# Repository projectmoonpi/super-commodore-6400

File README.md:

<p align="center"><b>Designed and Created by Project Moon Pi</b></p>

# Tidal Array 6400

Several **NTSC Commodore 64s** joined into one machine. Each C64 is a "core". One leader hands out work, and
every core, the leader included, computes its share. The goal is a pack of 8 or more C64s, sharing RAM through
a cartridge-port hub and running from one clock. Each machine added should make the whole thing about that much
faster, and the benchmark shows it on screen.

It is one of the [Project Moon Pi Commodore projects](https://github.com/projectmoonpi/commodore).

**Step 1 (this release): two C64s on a user-port cable.** It has the core kernel, the job protocol, and a
Mandelbrot benchmark with a live speed-up readout.

*Left: the leader's screen after the two-core run. The leader's own tiles are blue and cyan; core 1's are red,
orange and yellow. Right: core 1's own monitor, showing only the tiles it computed. Both are rendered from the
two-machine simulator's memory.*

## Results

| Cores | Simulator | VICE (real C64 timing) | Speed-up |
|---|---|---|---|
| 1 | 56.3 s | 60.2 s | 1.00× |
| 2 | 28.8 s | not tested: VICE can't link two C64s | **1.955×** |

That's 97.8% of a perfect doubling. The rest is the time spent passing tiles over the cable and the moment at
the end when one core finishes before the other.

The simulator doesn't count the cycles the VIC chip steals for the screen. That's the 7% gap on one core. Every
core loses the same share, so the speed-up is unchanged.

## What you need

- 2 NTSC C64s, each able to load the programs. Any of these works:
  - a disk drive with `ta6400.d64`, or an SD2IEC / Pi1541;
  - the `.prg` files on a Kung Fu Flash or other SD cartridge;
  - the cartridge images: `ta6400-leader.crt` and `ta6400-core.crt`. These are Magic Desk cartridges (32 KB
    and 16 KB) for a Kung Fu Flash, or burned to a Magic Desk-compatible EPROM cartridge. They start the
    program at power-on, and the reset button starts it again.
- A user-port-to-user-port cable (below).

## The cable

**Build it with the illustrated guide:
[Build Guide 1: the user-port link cable (PDF)](docs/guides/TA6400-Guide-1-Link-Cable.pdf).** It covers your
start and end goals, drawings of the finished cable and of the two C64s hooked up, a schematic, the parts
with DigiKey part numbers, how to find pin 1 on your C64, colour-coded wiring
and solder maps, numbered steps, a digital-multimeter test checklist, the first run, and troubleshooting. The table below
is the short version.

Two 24-pin (2×12, 0.156") user-port edge connectors, wired:

| Signal | C64 A pin | C64 B pin |
|---|---|---|
| PB0–PB7 (data) | C, D, E, F, H, J, K, L | C, D, E, F, H, J, K, L (straight through) |
| PC2 → FLAG | 8 | B |
| FLAG ← PC2 | B | 8 |
| GND | 1, 12, A, N | 1, 12, A, N |

Leave everything else unconnected. Never connect +5 V (pin 2), RESET (3) or 9 V AC (10, 11).

For safety, put a 330 Ω resistor in series with each data line (PB0–PB7). If a program ever drove the lines
from both ends at once, the resistors limit the current. The protocol never does this (the simulator counts
it, and it stayed at 0), but other software could. The resistors don't slow the link.

## Running it

1. Switch on the worker C64 and load the core: `LOAD"PACK CORE",8` then `RUN`, or plug in the core cartridge. It shows **CORE: WAITING FOR THE
   LEADER**.
2. On the leader C64: `LOAD"PACK LEADER",8` then `RUN`, or use the leader cartridge. It scans the cable, uploads the job to the core, and
   shows **CORES 2**. The core's screen changes to **CORE 1: LINKED TO THE LEADER**.
3. Press **1** to run on the leader alone, then **2** to run on both. Each result shows its time and its
   speed-up over the 1-core run. Press **S** to scan the cable again, for example after switching a core on.

## How it works

**The link.** Port B of CIA 2 carries 8 data bits. Every read or write of port B pulses PC2, which the other
machine sees on its FLAG input:
- writing a byte says "here is a byte";
- reading it says "got it".

That gives a fully handshaked byte transfer of about 30 cycles, around 30 KB/s. The leader drives the data
lines. When a core answers, the two sides hand the lines over with a "line free" pulse, so they never drive
at the same time.

**The core kernel** (`src/common.asm`) is a few hundred bytes. It obeys three commands:

| Command | Bytes | What the core does |
|---|---|---|
| WRITE | `$01` addr len data… | stores the data in its memory |
| READ | `$02` addr len | sends that memory back |
| CALL | `$03` addr A | runs `JSR addr` with A, then pulses "done" |

The cores are generic: the leader uploads the job (5 KB) when it finds a core. The same program could hand
out any other work.

**The benchmark** (`src/job.asm`) draws the whole Mandelbrot set at 160×160 multicolour pixels, in 200 tiles
of 16×8.
- Tiles are handed out one at a time, to whichever core is free, so fast and slow tiles balance out.
- The leader computes tiles too. After every 4 pixels it checks the cable. When the core says "done", the
  leader collects the tile's 32 bytes and gives the core the next one.
- Maths: 8.8 fixed point, at about 200 cycles an iteration. While a point is in play |z| < 2, so each value's
  high byte is 0 or 1. A square is then a table look-up, and a product is one 8×8 quarter-square multiply.

**Timing.** CIA 1's timer A counts cycles and timer B counts timer A's underflows, giving an exact 32-bit
cycle count.

## Building and testing

`./build.sh` assembles everything with ACME, writes `build/ta6400.d64` and the two cartridge images
(`src/cart.asm`, `tools/make_crt.py`), and runs the test.

VICE 3.8 can't connect two C64s through their user ports. So `tools/packsim.c` simulates two C64s joined by
the cable:
- a 6510 with all documented opcodes and cycle counts;
- the memory map, CIA timers and raster interrupts;
- port B, PC2 and FLAG, wired as above.

`tools/simcheck.py` then checks the result:
- runs the auto-test leader (`-DAUTO=1`: 1 core, then all cores);
- compares every tile with a Python copy of the job's maths;
- counts which core did which tile;
- reports any contention on the cable;
- writes `build/sim-0.png` and `build/sim-1.png`.

The leader's picture from VICE matches the simulator's byte for byte.

## Roadmap

1. **Two C64s, user-port cable.** Software, protocol and benchmark. *This release: tested in simulation and in
   VICE; real hardware next.*
2. **Clock-injection bench test.** One 14.31818 MHz master clock fed to two C64s, with the crystal left in
   place but bypassed. The mod board must suit every motherboard revision (250407, 250425, 250466 and 250469),
   set with a switch or jumpers. The test also checks that the hub can line the machines up by dropping clock
   pulses.
3. **Pack Link pod and a 2-port hub.** A cartridge-port pod in each C64, ribbon cables, and an FPGA hub with
   fast shared SRAM, mailboxes and IRQs. That gives full-speed shared memory instead of a cable.
4. **The 8-port hub.** An 8-core benchmark and the video wall.

## Credits

- **Design, code and the Project Moon Pi logo.** Project Moon Pi.
- **Character set.** Copied at run time from the C64's own character ROM (© Commodore). It is not included
  here. The simulator reads VICE's copy for its renders.
- **ACME** cross-assembler. Marco Baye and contributors (GPL).
- **VICE** emulator and `c1541`. The VICE team (GPL).
- **Python and Pillow.** Their authors (PSF / HPND licences).
- **Palette values.** The "colodore" C64 palette by Philip "Pepto" Timmermann.
- **B612 typeface** (the build guide's cover). Airbus and Intactile Design (SIL Open Font License 1.1, see
  `tools/guide/fonts/OFL.txt`).
- **ReportLab** (the build guide). ReportLab Inc. (BSD).
- **Quarter-square multiplication.** A classic 6502 technique, as documented on codebase64.org.
- **User port pinout and CIA behaviour.** The *Commodore 64 Programmer's Reference Guide* and the MOS 6526
  datasheet.
- Built with Claude Code (Anthropic).

Commodore 64 is a trademark of its owners. Project Moon Pi is not affiliated with them.

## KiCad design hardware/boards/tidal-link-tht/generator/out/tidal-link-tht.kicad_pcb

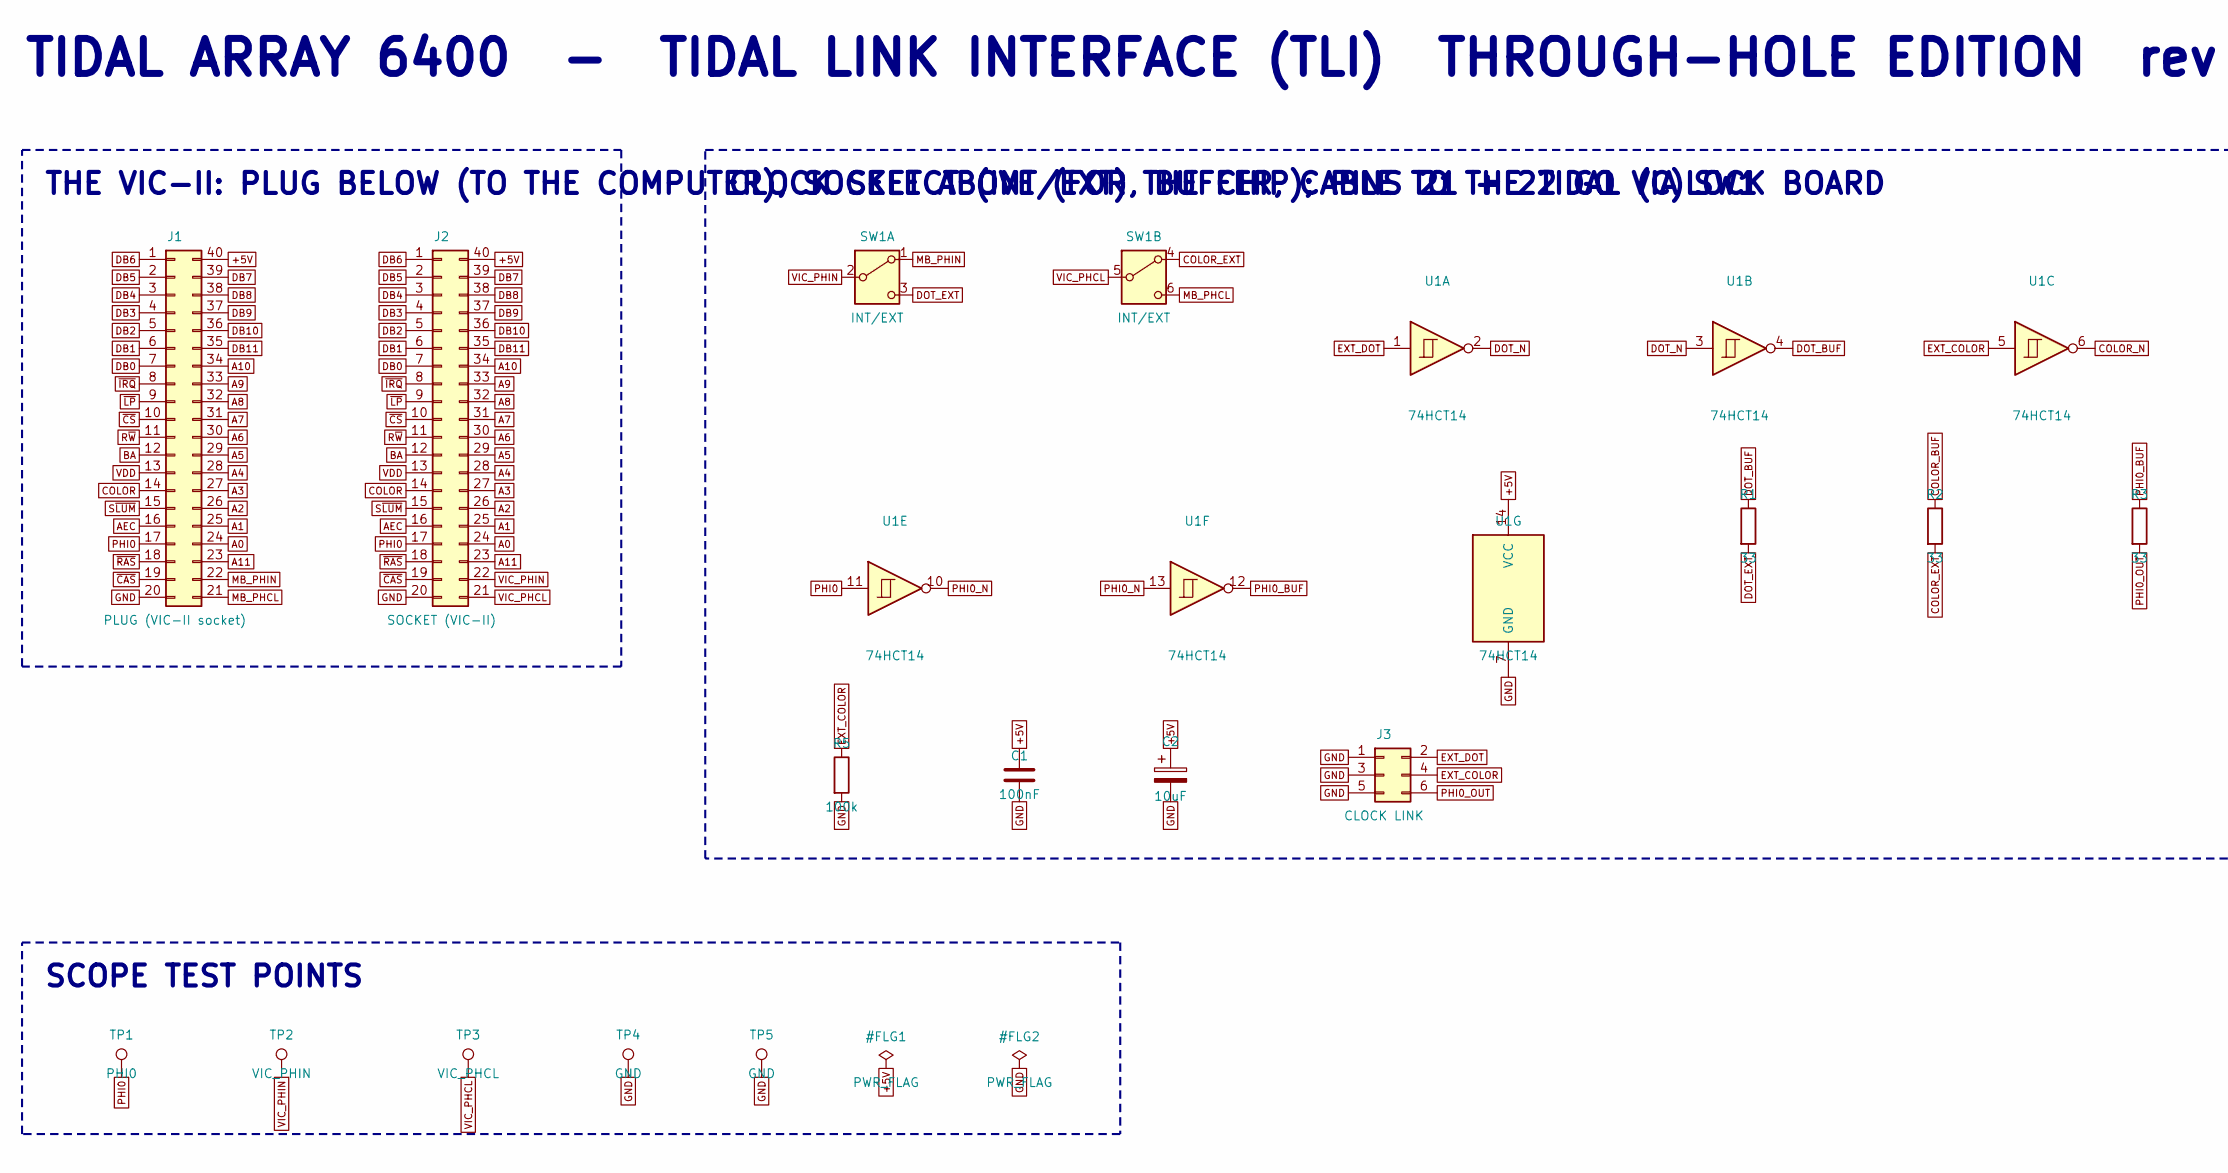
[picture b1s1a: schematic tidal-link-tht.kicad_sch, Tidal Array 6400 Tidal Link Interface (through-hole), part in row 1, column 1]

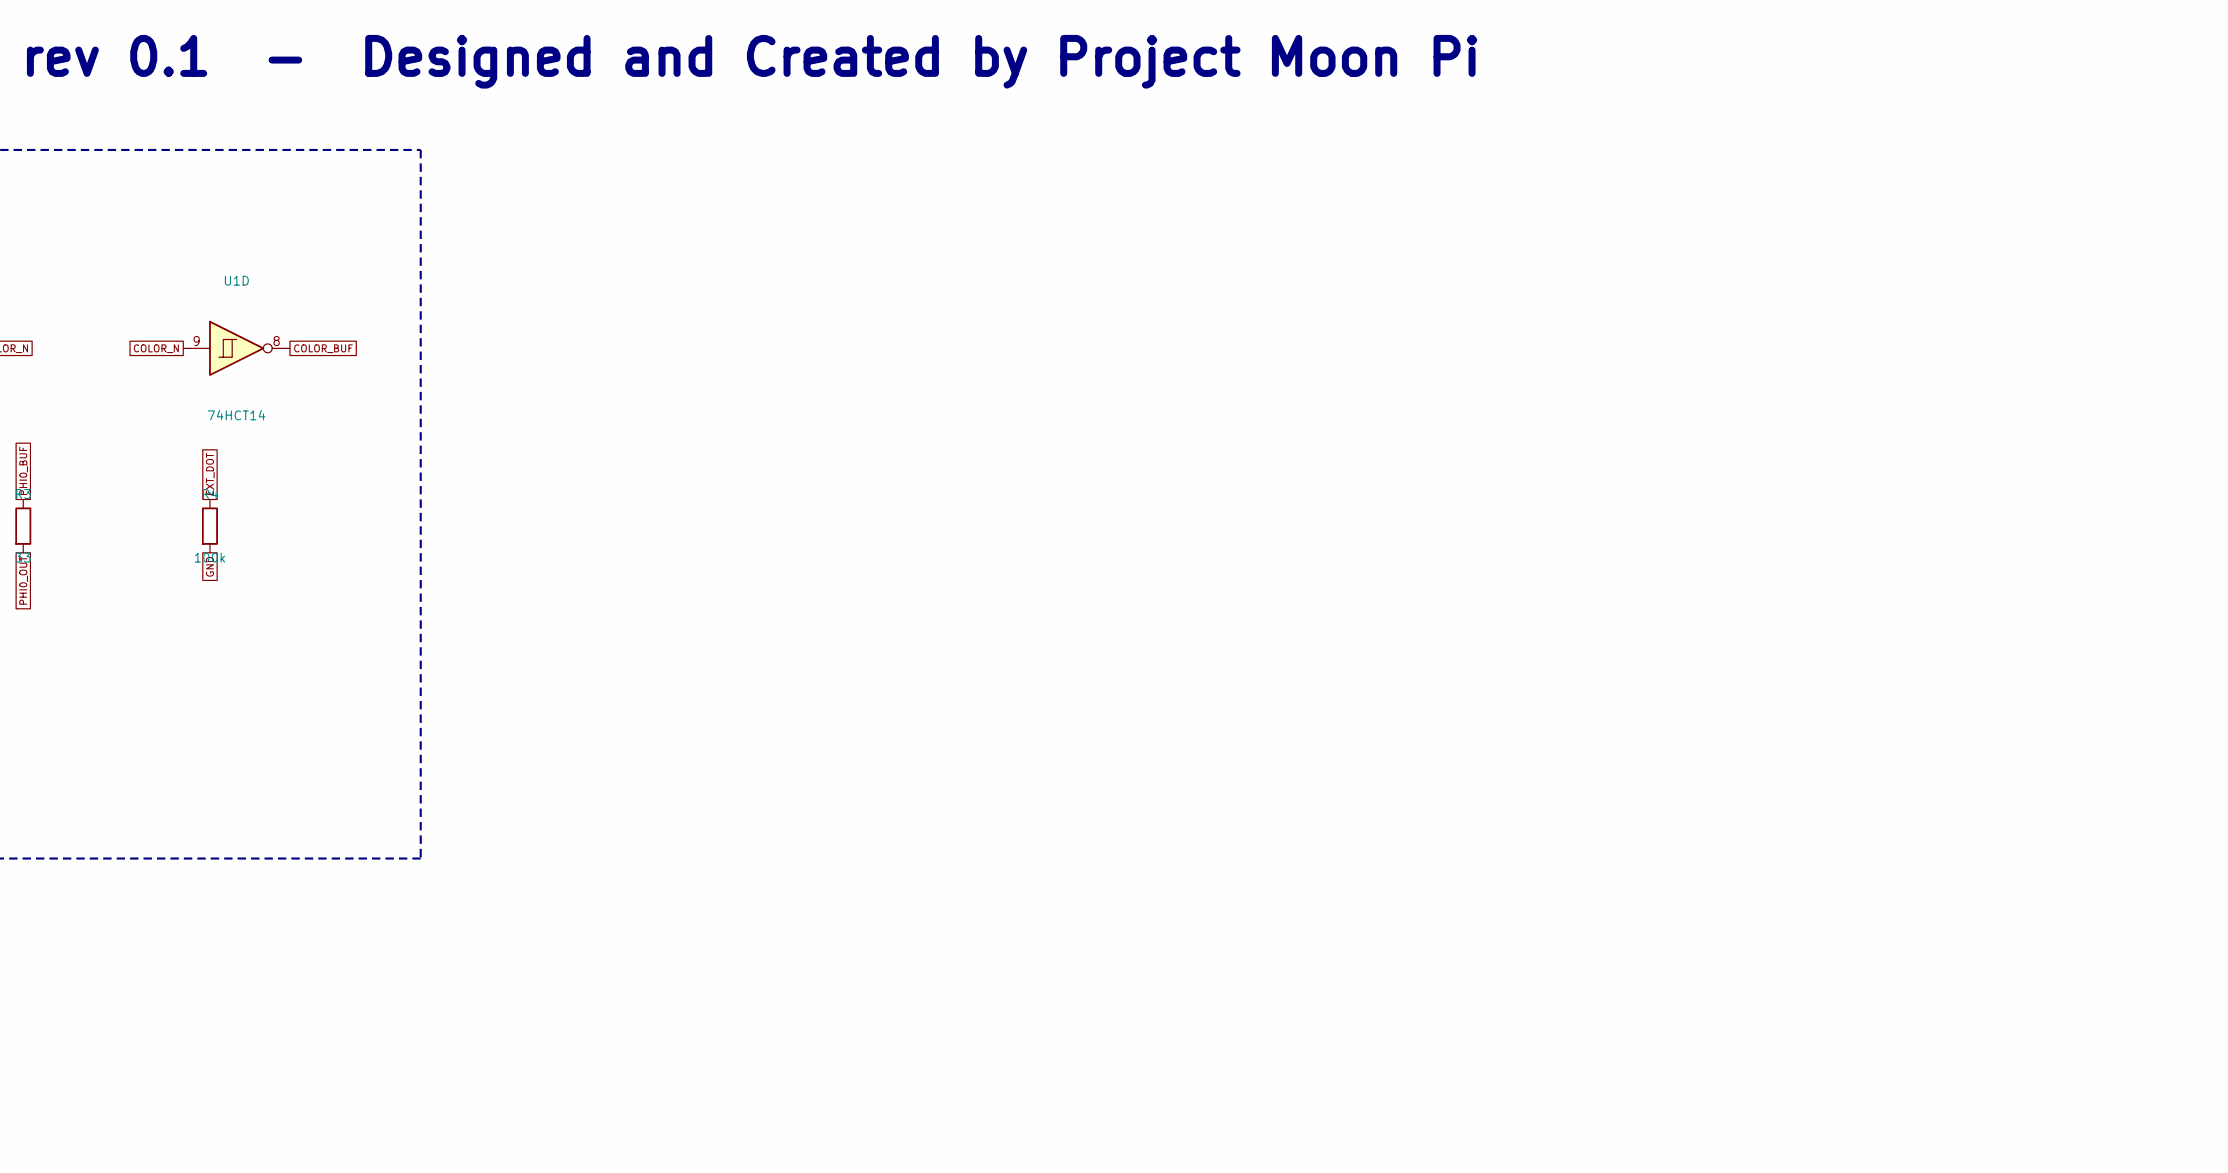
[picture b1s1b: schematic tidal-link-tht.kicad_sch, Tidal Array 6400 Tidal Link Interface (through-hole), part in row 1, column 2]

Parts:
C1: 100nF; C_Rect_L4.0mm_W2.5mm_P2.50mm; MPN FG18X7R1H104KNT06
C2: 10uF; CP_Radial_D5.0mm_P2.00mm; MPN ESK106M025AC3AA
J1: PLUG (VIC-II socket); DIP-40_W15.24mm; MPN 350-10-164-00-006000 (one 64-pin strip,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
J2: SOCKET (VIC-II); DIP-40_W15.24mm; MPN 310-87-120-41-001101 (x2)
J3: CLOCK LINK; IDC-Header_2x03_P2.54mm_Vertical; MPN 61200621621
R1, R2, R3: 33; R_Axial_DIN0207_L6.3mm_D2.5mm_P7.62mm_Horizontal; MPN MFR-25FBF52-33R
R4, R5: 100k; R_Axial_DIN0207_L6.3mm_D2.5mm_P7.62mm_Horizontal; MPN MFR-25FRF52-100K
SW1: INT/EXT; SW_CK_JS202011CQN_DPDT_Straight; MPN JS202011CQN
TP1: PHI0; TestPoint_Keystone_5000-5004_Miniature; MPN 5002
TP2: VIC_PHIN; TestPoint_Keystone_5000-5004_Miniature; MPN 5004
TP3: VIC_PHCL; TestPoint_Keystone_5000-5004_Miniature; MPN 5003
TP4, TP5: GND; TestPoint_Keystone_5000-5004_Miniature; MPN 5001
U1: 74HCT14; DIP-14_W7.62mm_Socket; MPN SN74HCT14N

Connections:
+5V: C1.1, C2.1, J1.40, J2.40, U1.14 (VCC)
A0: J1.24, J2.24
A1: J1.25, J2.25
A2: J1.26, J2.26
A3: J1.27, J2.27
A4: J1.28, J2.28
A5: J1.29, J2.29
A6: J1.30, J2.30
A7: J1.31, J2.31
A8: J1.32, J2.32
A9: J1.33, J2.33
A10: J1.34, J2.34
A11: J1.23, J2.23
AEC: J1.16, J2.16
BA: J1.12, J2.12
COLOR: J1.14, J2.14
COLOR_BUF: R2.1, U1.8
COLOR_EXT: R2.2, SW1.4 (A)
COLOR_N: U1.6, U1.9
DB0: J1.7, J2.7
DB1: J1.6, J2.6
DB2: J1.5, J2.5
DB3: J1.4, J2.4
DB4: J1.3, J2.3
DB5: J1.2, J2.2
DB6: J1.1, J2.1
DB7: J1.39, J2.39
DB8: J1.38, J2.38
DB9: J1.37, J2.37
DB10: J1.36, J2.36
DB11: J1.35, J2.35
DOT_BUF: R1.1, U1.4
DOT_EXT: R1.2, SW1.3 (C)
DOT_N: U1.2, U1.3
EXT_COLOR: J3.4, R5.1, U1.5
EXT_DOT: J3.2, R4.1, U1.1
GND: C1.2, C2.2, J1.20, J2.20, J3.1, J3.3, J3.5, R4.2, R5.2, TP4.1, TP5.1, U1.7 (GND)
MB_PHCL: J1.21, SW1.6 (C)
MB_PHIN: J1.22, SW1.1 (A)
PHI0: J1.17, J2.17, TP1.1, U1.11
PHI0_BUF: R3.1, U1.12
PHI0_N: U1.10, U1.13
PHI0_OUT: J3.6, R3.2
R~W: J1.11, J2.11
S~LUM: J1.15, J2.15
VDD: J1.13, J2.13
VIC_PHCL: J2.21, SW1.5 (B), TP3.1
VIC_PHIN: J2.22, SW1.2 (B), TP2.1
~CAS: J1.19, J2.19
~CS: J1.10, J2.10
~IRQ: J1.8, J2.8
~LP: J1.9, J2.9
~RAS: J1.18, J2.18

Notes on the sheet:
THE VIC-II: PLUG BELOW (TO THE COMPUTER), SOCKET ABOVE (FOR THE CHIP); PINS 21 + 22 GO VIA SW1
CLOCK SELECT (INT/EXT), BUFFER, CABLE TO THE TIDAL (C)LOCK BOARD
SCOPE TEST POINTS
TIDAL ARRAY 6400 - TIDAL LINK INTERFACE (TLI) THROUGH-HOLE EDITION rev 0.1 - Designed and Created by Project Moon Pi

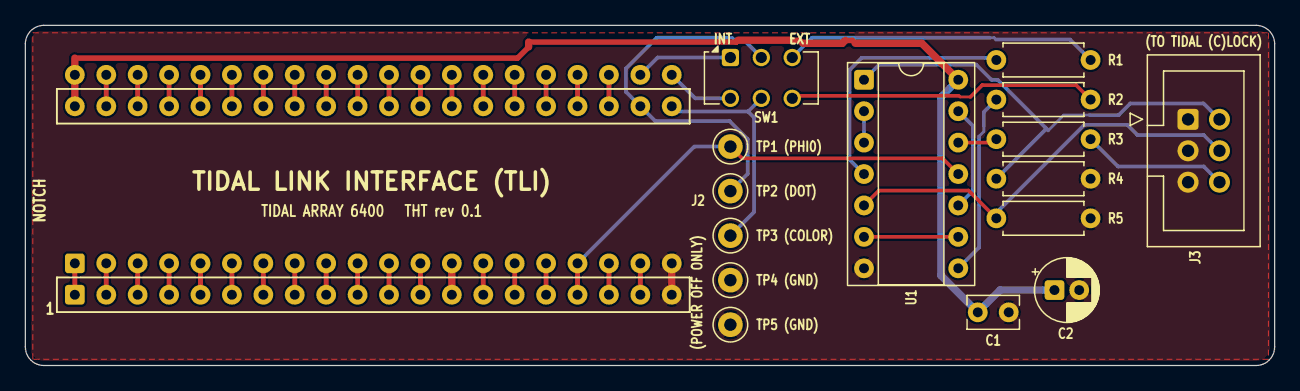
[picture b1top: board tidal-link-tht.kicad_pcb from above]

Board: 2 copper layers, 101.0 x 27.5 mm, 17 parts (0 on the bottom side), 53 nets.

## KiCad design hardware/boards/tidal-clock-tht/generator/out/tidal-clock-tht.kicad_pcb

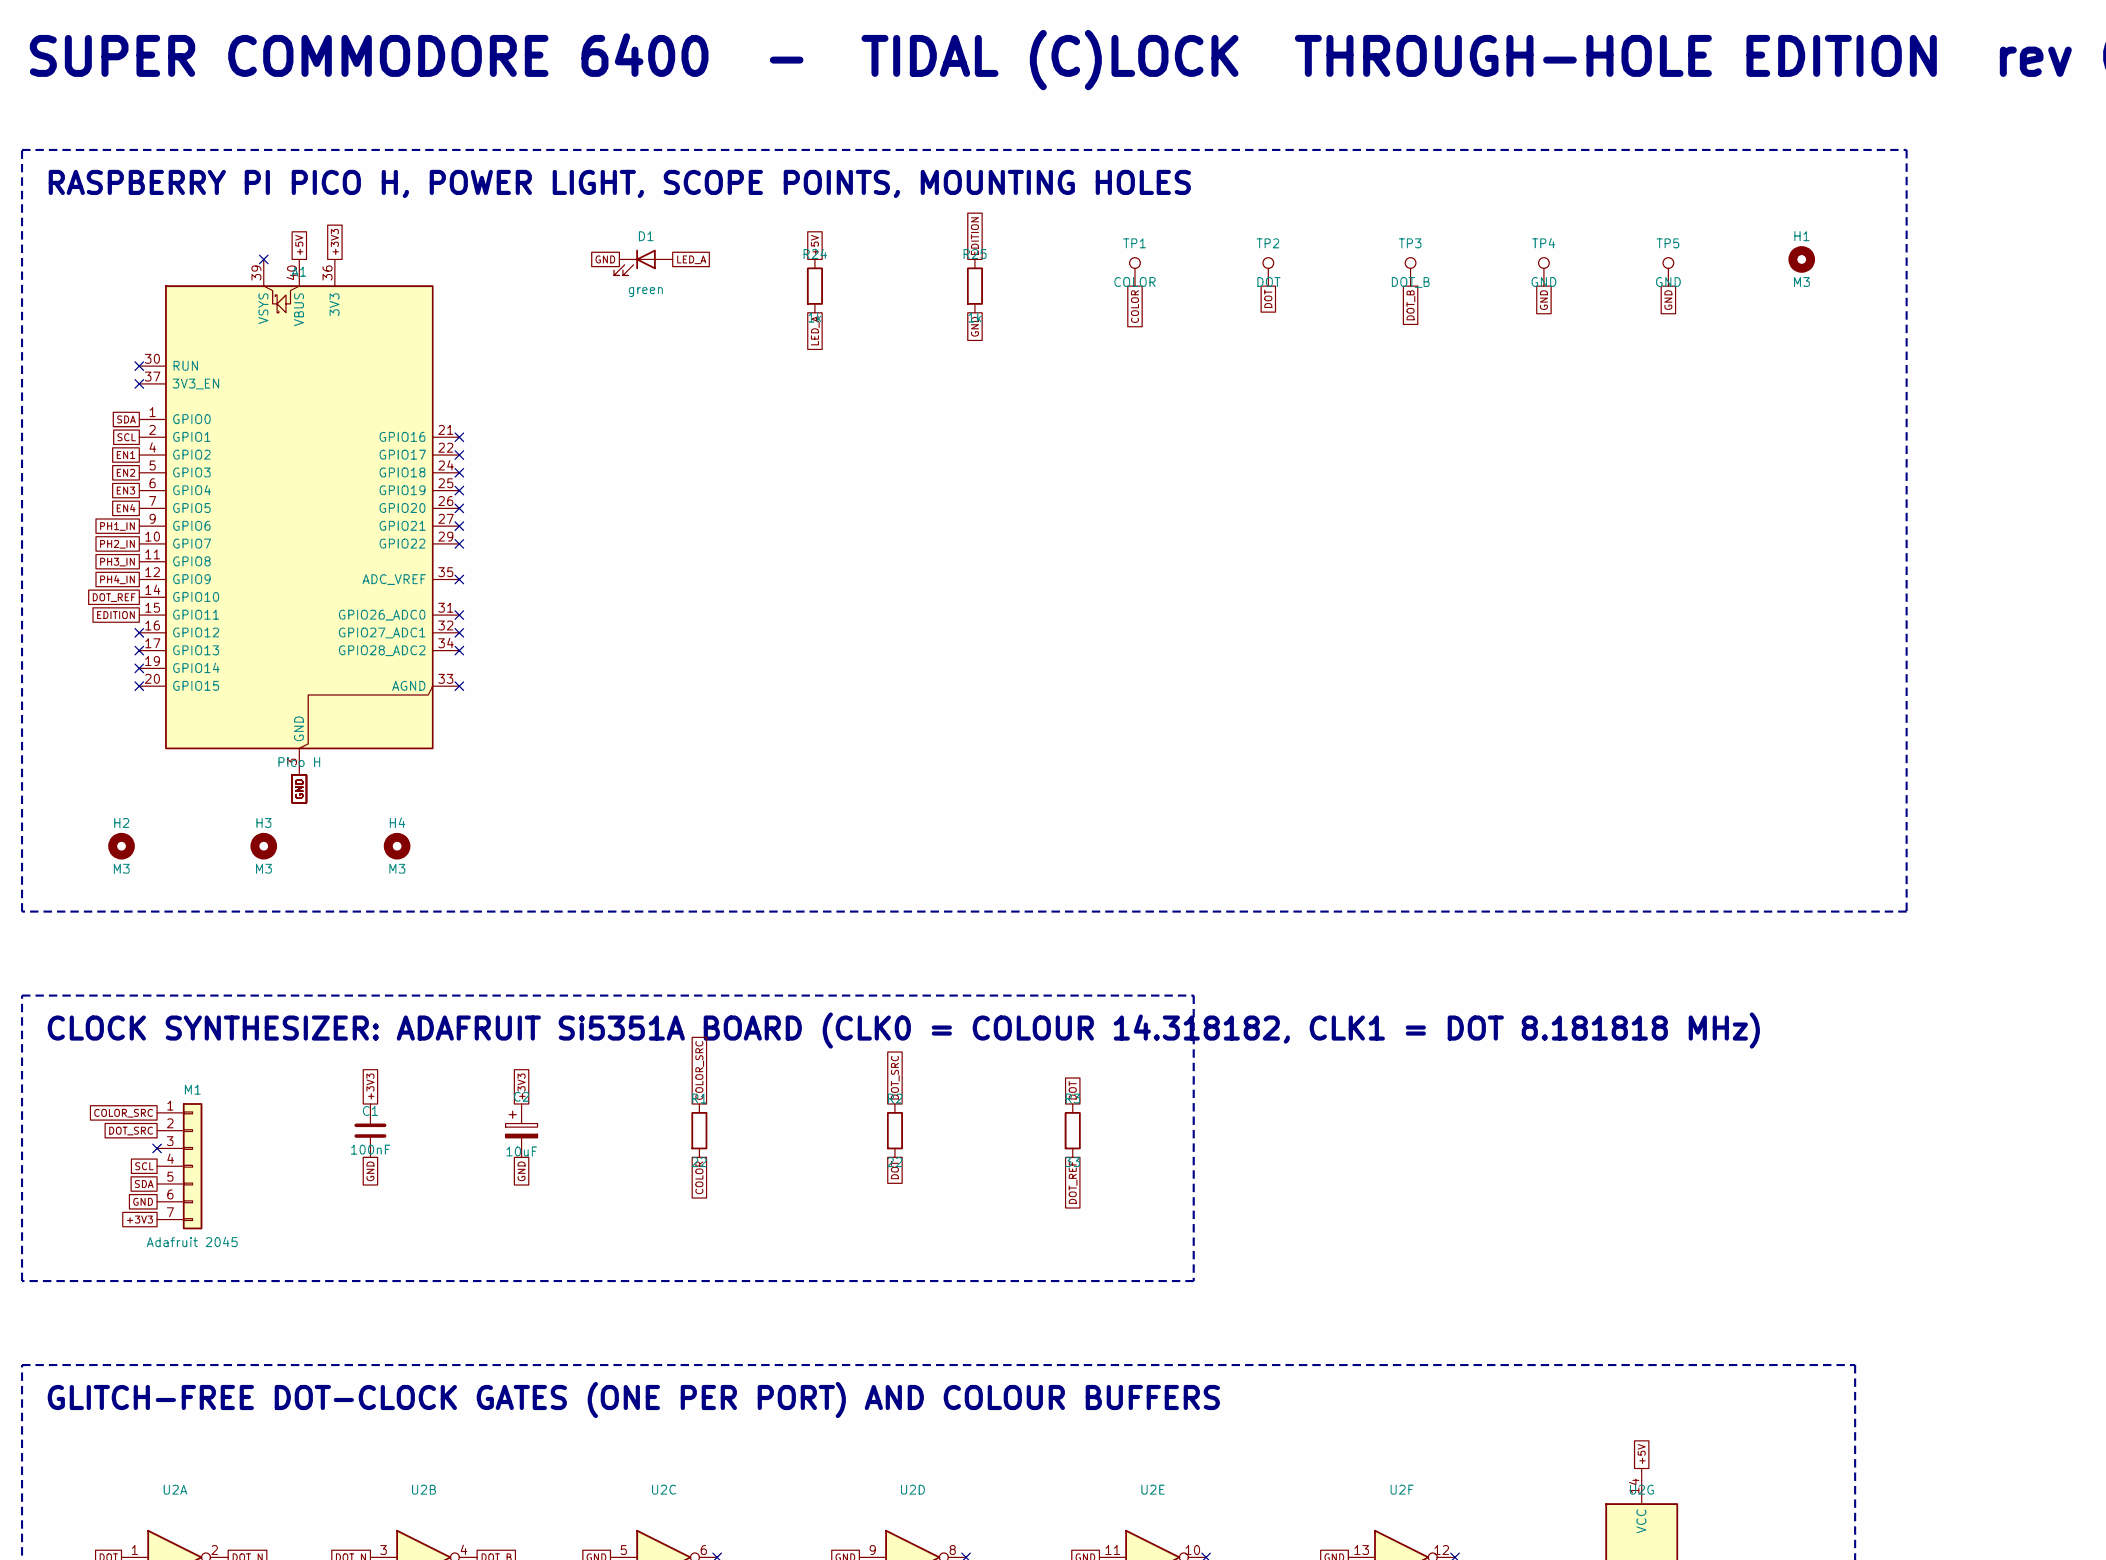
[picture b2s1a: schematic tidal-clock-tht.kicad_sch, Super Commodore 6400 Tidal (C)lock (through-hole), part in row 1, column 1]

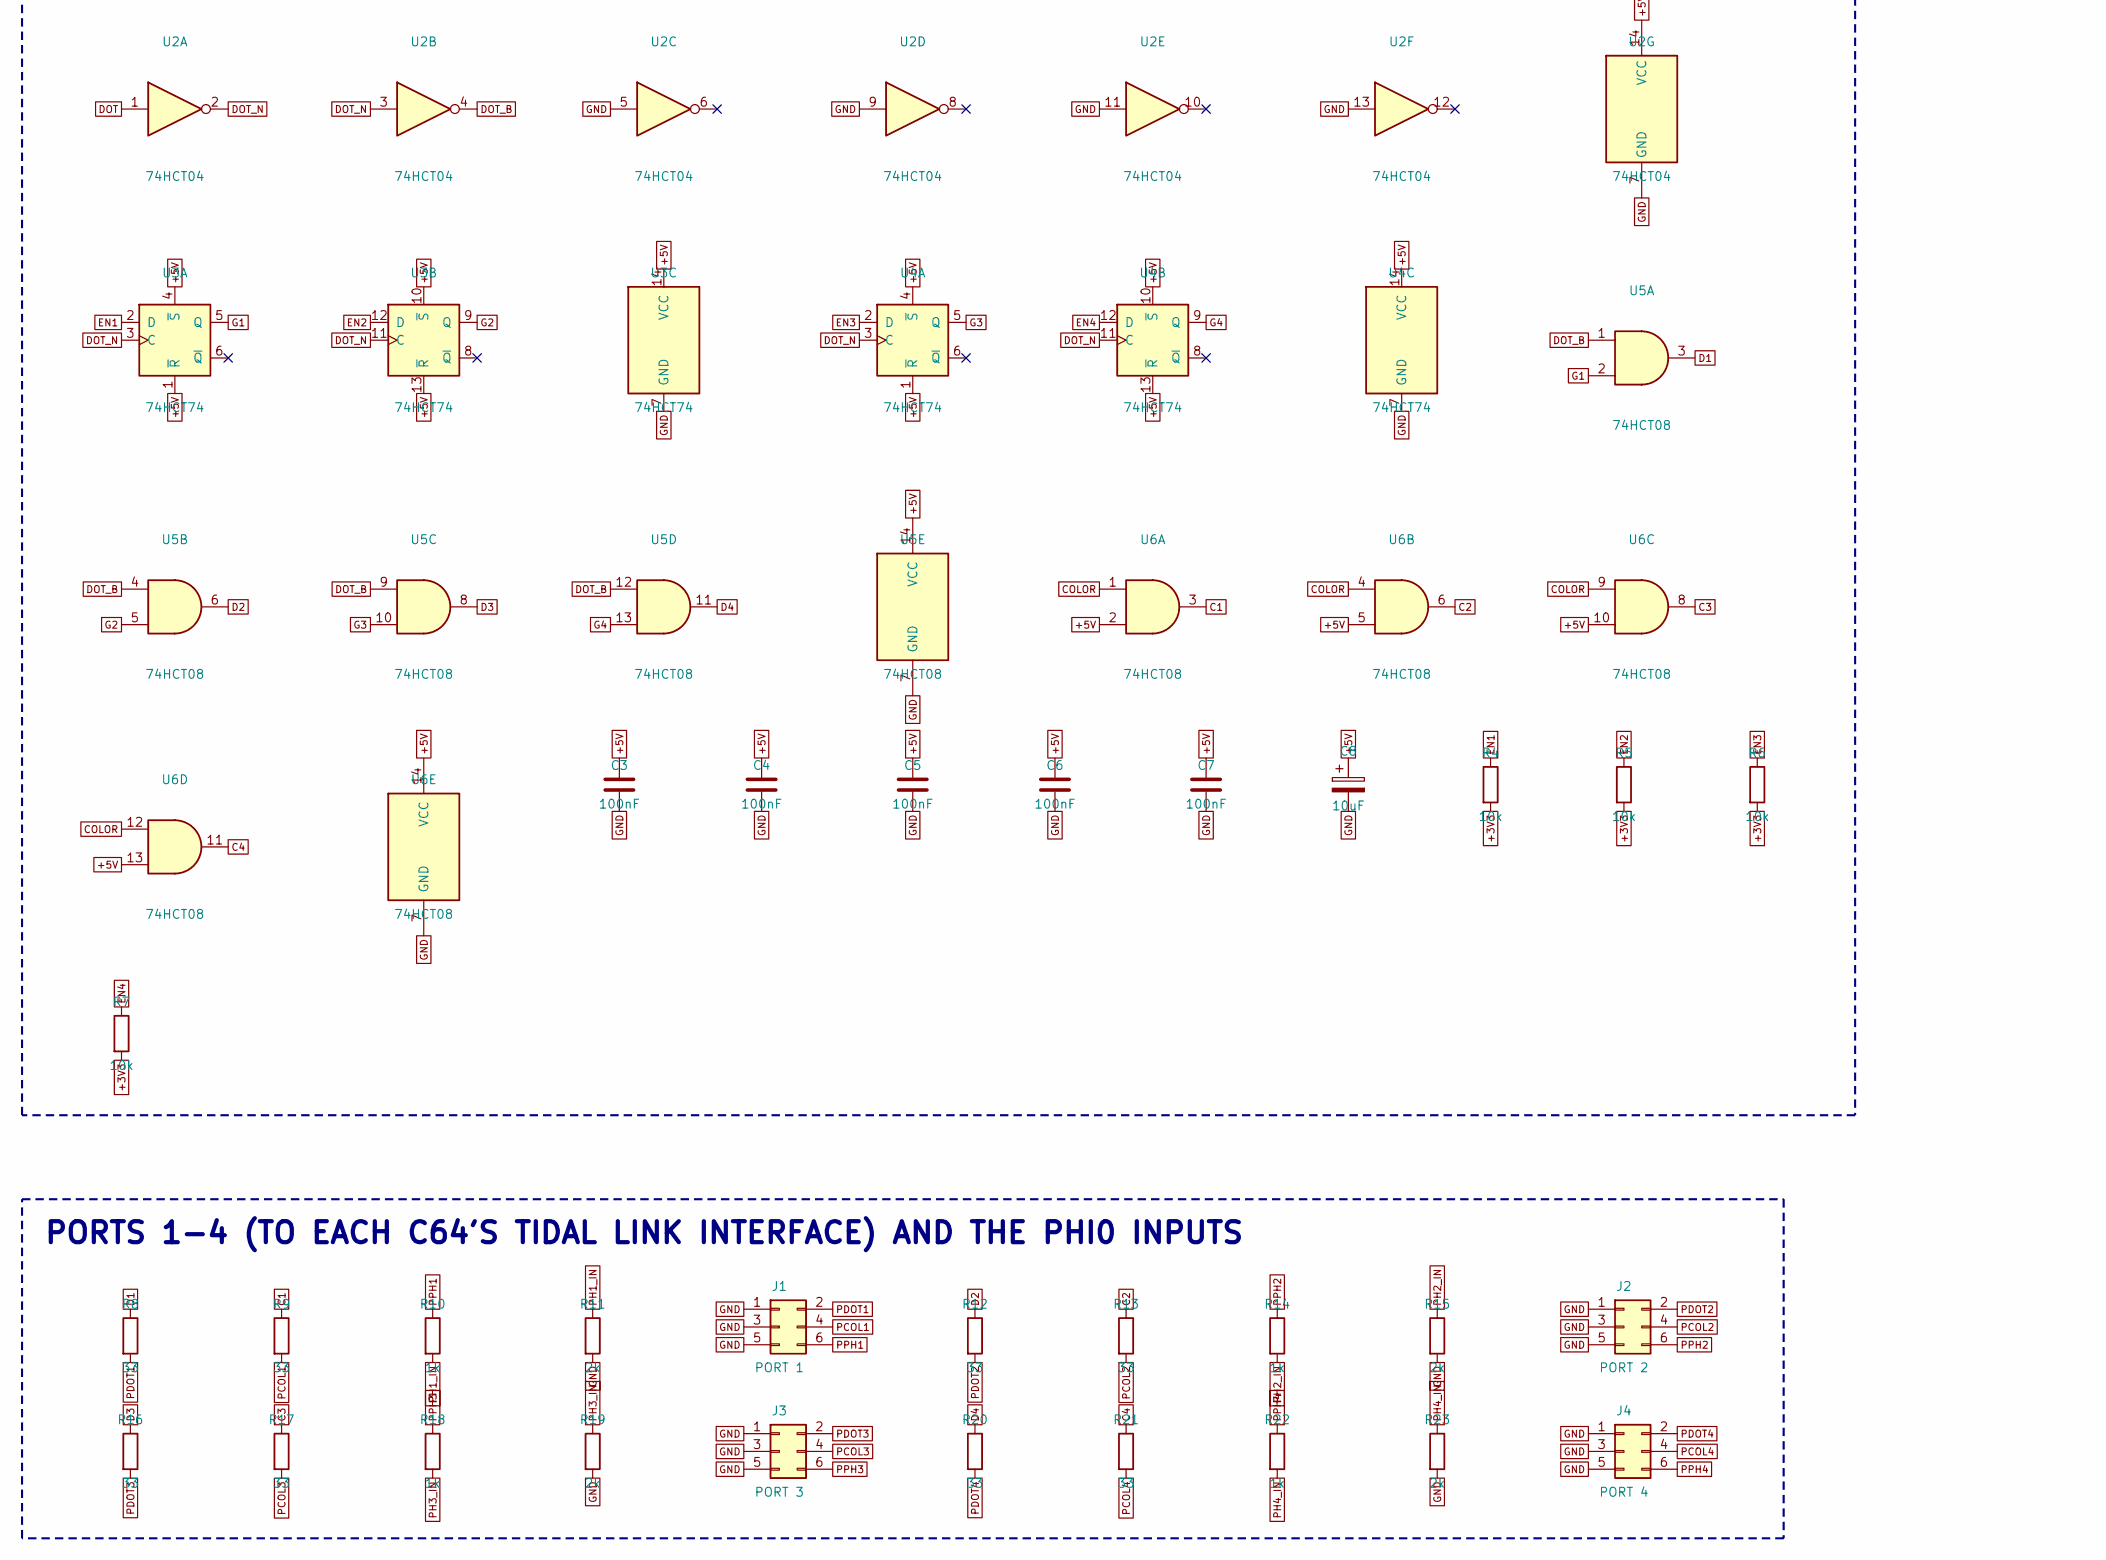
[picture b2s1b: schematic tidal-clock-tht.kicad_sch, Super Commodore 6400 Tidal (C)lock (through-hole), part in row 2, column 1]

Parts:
A1: Pico H; RaspberryPi_Pico_Common_THT; MPN SC0917
C1, C3, C4, C5, C6, C7: 100nF; C_Rect_L4.0mm_W2.5mm_P2.50mm; MPN FG18X7R1H104KNT06
C2, C8: 10uF; CP_Radial_D5.0mm_P2.00mm; MPN ESK106M025AC3AA
D1: green; LED_D3.0mm; MPN LTL-4231N
H1, H2, H3, H4: M3; MountingHole_3.2mm_M3
J1: PORT 1; IDC-Header_2x03_P2.54mm_Vertical; MPN 61200621621
J2: PORT 2; IDC-Header_2x03_P2.54mm_Vertical; MPN 61200621621
J3: PORT 3; IDC-Header_2x03_P2.54mm_Vertical; MPN 61200621621
J4: PORT 4; IDC-Header_2x03_P2.54mm_Vertical; MPN 61200621621
M1: Adafruit 2045; PinSocket_1x07_P2.54mm_Vertical; MPN 2045
R1, R2: 22; R_Axial_DIN0207_L6.3mm_D2.5mm_P10.16mm_Horizontal; MPN MFR-25FBF52-22R
R3, R8, R9, R12, R13, R16, R17, R20, R21: 33; R_Axial_DIN0207_L6.3mm_D2.5mm_P10.16mm_Horizontal; MPN MFR-25FBF52-33R
R4, R5, R6, R7: 10k; R_Axial_DIN0207_L6.3mm_D2.5mm_P10.16mm_Horizontal; MPN MFR-25FBF52-10K
R10, R14, R18, R22, R24, R25: 1k; R_Axial_DIN0207_L6.3mm_D2.5mm_P10.16mm_Horizontal; MPN MFR-25FBF52-1K
R11, R15, R19, R23: 2k; R_Axial_DIN0207_L6.3mm_D2.5mm_P10.16mm_Horizontal; MPN MFR-25FBF52-2K
TP1: COLOR; TestPoint_Keystone_5000-5004_Miniature; MPN 5003
TP2: DOT; TestPoint_Keystone_5000-5004_Miniature; MPN 5004
TP3: DOT_B; TestPoint_Keystone_5000-5004_Miniature; MPN 5002
TP4, TP5: GND; TestPoint_Keystone_5000-5004_Miniature; MPN 5001
U2: 74HCT04; DIP-14_W7.62mm_Socket; MPN SN74HCT04N
U3, U4: 74HCT74; DIP-14_W7.62mm_Socket; MPN SN74HCT74N
U5, U6: 74HCT08; DIP-14_W7.62mm_Socket; MPN SN74HCT08N

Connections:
+3V3: A1.36 (3V3), C1.1, C2.1, M1.7, R4.2, R5.2, R6.2, R7.2
+5V: A1.40 (VBUS), C3.1, C4.1, C5.1, C6.1, C7.1, C8.1, R24.1, U2.14 (VCC), U3.1 (~R), U3.4 (~S), U3.10 (~S), U3.13 (~R), U3.14 (VCC), U4.1 (~R), U4.4 (~S), U4.10 (~S), U4.13 (~R), U4.14 (VCC), U5.14 (VCC), U6.2, U6.5, U6.10, U6.13, U6.14 (VCC)
C1: R9.1, U6.3
C2: R13.1, U6.6
C3: R17.1, U6.8
C4: R21.1, U6.11
COLOR: R1.2, TP1.1, U6.1, U6.4, U6.9, U6.12
COLOR_SRC: M1.1, R1.1
D1: R8.1, U5.3
D2: R12.1, U5.6
D3: R16.1, U5.8
D4: R20.1, U5.11
DOT: R2.2, R3.1, TP2.1, U2.1
DOT_B: TP3.1, U2.4, U5.1, U5.4, U5.9, U5.12
DOT_N: U2.2, U2.3, U3.3 (C), U3.11 (C), U4.3 (C), U4.11 (C)
DOT_REF: A1.14 (GPIO10), R3.2
DOT_SRC: M1.2, R2.1
EDITION: A1.15 (GPIO11), R25.1
EN1: A1.4 (GPIO2), R4.1, U3.2 (D)
EN2: A1.5 (GPIO3), R5.1, U3.12 (D)
EN3: A1.6 (GPIO4), R6.1, U4.2 (D)
EN4: A1.7 (GPIO5), R7.1, U4.12 (D)
G1: U3.5 (Q), U5.2
G2: U3.9 (Q), U5.5
G3: U4.5 (Q), U5.10
G4: U4.9 (Q), U5.13
GND: A1.3 (GND), A1.8 (GND), A1.13 (GND), A1.18 (GND), A1.23 (GND), A1.28 (GND), A1.38 (GND), C1.2, C2.2, C3.2, C4.2, C5.2, C6.2, C7.2, C8.2, D1.1 (K), J1.1, J1.3, J1.5, J2.1, J2.3, J2.5, J3.1, J3.3, J3.5, J4.1, J4.3, J4.5, M1.6, R11.2, R15.2, R19.2, R23.2, R25.2, TP4.1, TP5.1, U2.5, U2.7 (GND), U2.9, U2.11, U2.13, U3.7 (GND), U4.7 (GND), U5.7 (GND), U6.7 (GND)
LED_A: D1.2 (A), R24.2
PCOL1: J1.4, R9.2
PCOL2: J2.4, R13.2
PCOL3: J3.4, R17.2
PCOL4: J4.4, R21.2
PDOT1: J1.2, R8.2
PDOT2: J2.2, R12.2
PDOT3: J3.2, R16.2
PDOT4: J4.2, R20.2
PH1_IN: A1.9 (GPIO6), R10.2, R11.1
PH2_IN: A1.10 (GPIO7), R14.2, R15.1
PH3_IN: A1.11 (GPIO8), R18.2, R19.1
PH4_IN: A1.12 (GPIO9), R22.2, R23.1
PPH1: J1.6, R10.1
PPH2: J2.6, R14.1
PPH3: J3.6, R18.1
PPH4: J4.6, R22.1
SCL: A1.2 (GPIO1), M1.4
SDA: A1.1 (GPIO0), M1.5

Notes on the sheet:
RASPBERRY PI PICO H, POWER LIGHT, SCOPE POINTS, MOUNTING HOLES
CLOCK SYNTHESIZER: ADAFRUIT Si5351A BOARD (CLK0 = COLOUR 14.318182, CLK1 = DOT 8.181818 MHz)
GLITCH-FREE DOT-CLOCK GATES (ONE PER PORT) AND COLOUR BUFFERS
PORTS 1-4 (TO EACH C64'S TIDAL LINK INTERFACE) AND THE PHI0 INPUTS
SUPER COMMODORE 6400 - TIDAL (C)LOCK THROUGH-HOLE EDITION rev 0.1 - Designed and Created by Project Moon Pi

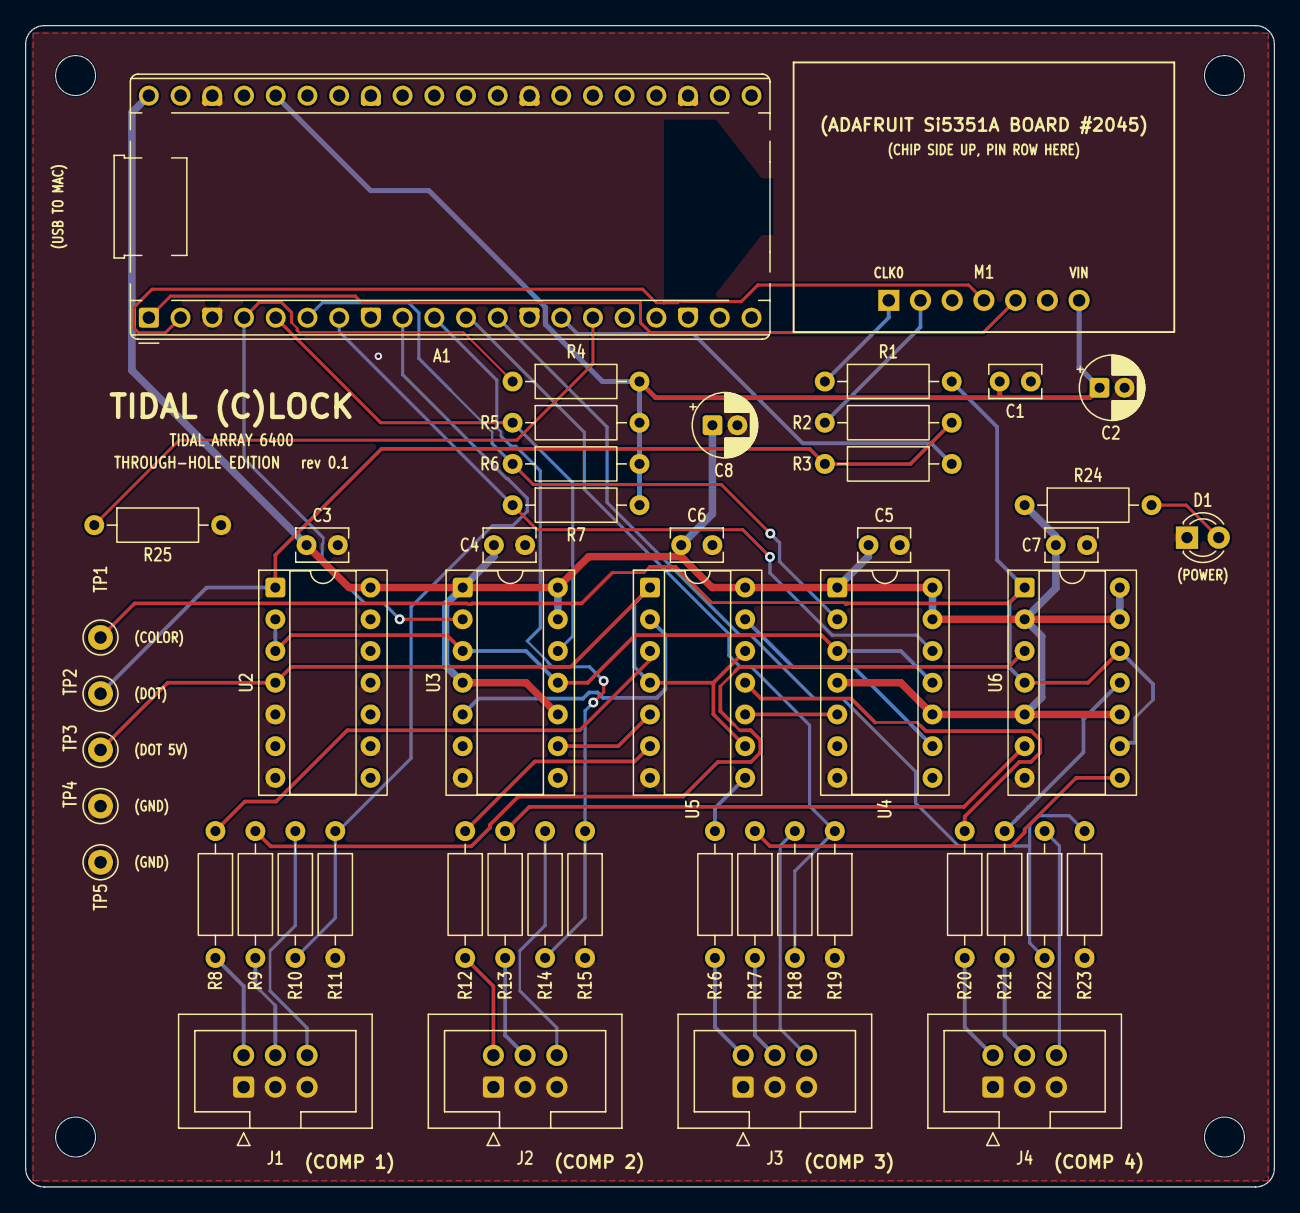
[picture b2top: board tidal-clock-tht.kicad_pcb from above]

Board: 2 copper layers, 100.0 x 93.0 mm, 54 parts (0 on the bottom side), 46 nets.
